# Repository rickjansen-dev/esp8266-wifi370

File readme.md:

esp8266-wifi370
==================

Implementation of the wifi370 protocol to connect cheap RGB ledstrips to pimatic using a esp8266.
Currently this repository contains the following:

 - Lua scripts to run on NodeMCU firmware
 - Eagle PCB schematic & board layout

## Quick how-to setup

- Install [pimatic] and the excellent [pimatic-led-light] plugin
- Install NodeMCU on the esp8266, connect it to your wifi & upload the lua scripts (ESPlorer is a nice tool to do this)

For the pimatic-led-light configuration, use wifi370 as the device parameter.
It's probably a good idea to set up your router's DHCP server so your esp8266 will get the same IP address every time.

## Eagle PCB schematic & board layout

There's a PCB schematic & board layout in the repository. The PCB contains the ESP-03, a voltage regulator, a power input & 3 logic gate MOSFETs to control the RGB channels of the ledstrip. See my blog at [auspex.nl] for a more detailed explanation.

## Demo video

I recorded a demonstration video, you can watch it [here].  
I am aware of VVS, it was just easier to get everything on screen and use my mouse at the same time =]

## Known bugs

- The PWM output sometimes glitches due to being software-based PWM. It only really flickers when moving from one color to another. 
- The output color is stored in the esp8266's flash memory. The pimatic-led-light UI can output a lot of values in a short amount of time which leads to lots of writes to the flash memory. I am unsure if this will be a problem and if the esp8266's flash can become corrupt. Use at your own risk.
- The on-off state might not always be in the correct state, as the wifi370 protocol implementation is very basic.

[pimatic]:http://pimatic.org
[pimatic-led-light]:https://github.com/philip1986/pimatic-led-light
[auspex.nl]:http://auspex.nl
[here]:http://youtu.be/MzmGHIzuEzY

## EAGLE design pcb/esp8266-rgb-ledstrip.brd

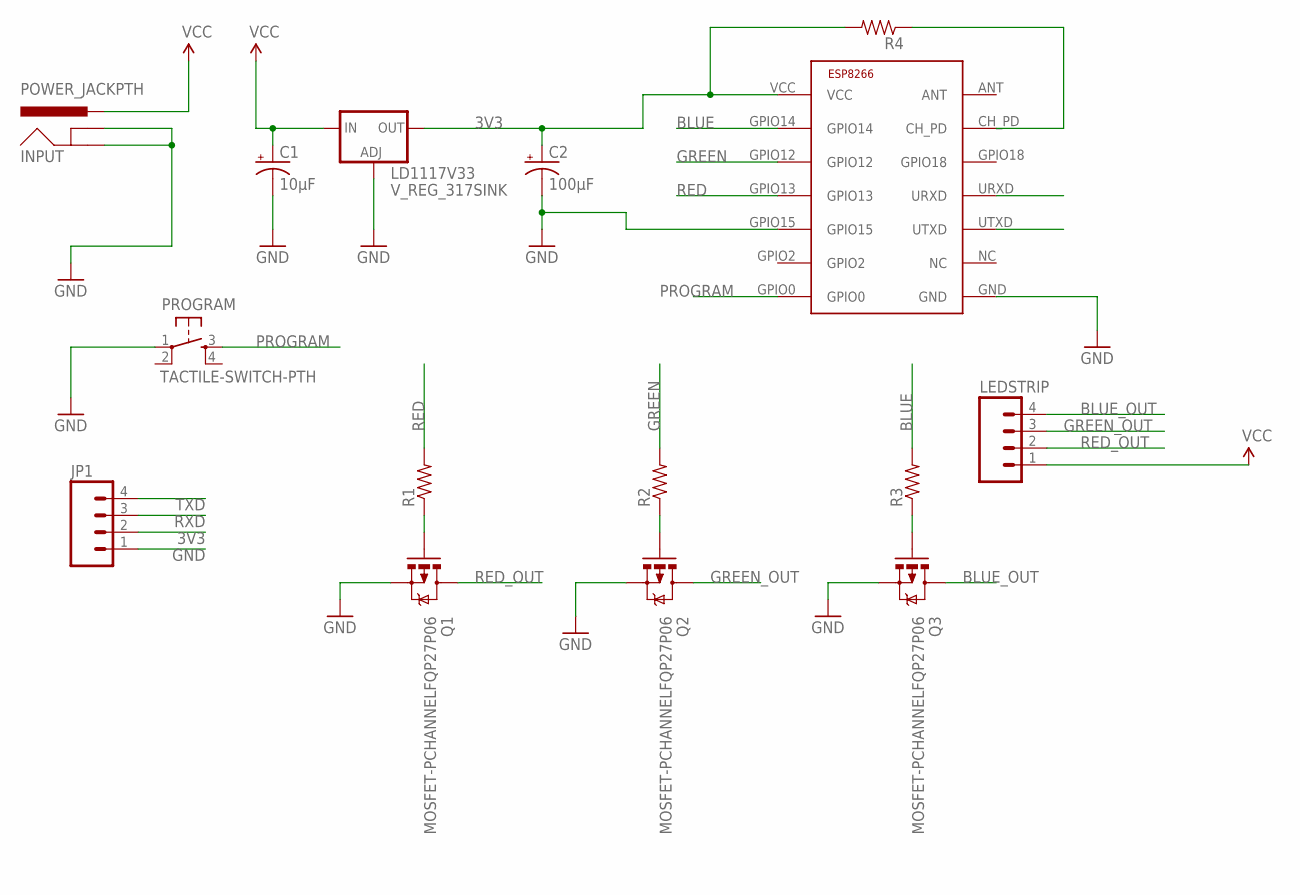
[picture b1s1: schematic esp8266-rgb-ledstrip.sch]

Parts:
C1: 10µF; CPOL-RADIAL-10UF-25V
C2: 100µF; CPOL-RADIAL-100UF-25V
INPUT: POWER_JACKPTH; POWER_JACK_PTH
JP1: M04PTH; 1X04
LD1117V33: V_REG_317SINK; TO220-ADJ
LEDSTRIP: M04PTH; 1X04
PROGRAM: TACTILE-SWITCH-PTH; TAC-SWITCH-PTH
Q1, Q2, Q3: MOSFET-PCHANNELFQP27P06; TO220V
R1, R2, R3, R4: RESISTORAXIAL-0.3; AXIAL-0.3
U$1: ESP8266-03; ESP-03

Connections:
3V3: C2.1 (+), JP1.2, LD1117V33.OUT, R4.P$2 (2), U$1.VCC
BLUE: R3.P$2 (2), U$1.GPIO14
BLUE_OUT: LEDSTRIP.4, Q3.2 (D)
BLUE_R: Q3.1 (G), R3.P$1 (1)
GND: C1.2 (-), C2.2 (-), INPUT.GND, INPUT.GNDBREAK, JP1.1, LD1117V33.ADJ, PROGRAM.1, Q1.3 (S), Q2.3 (S), Q3.3 (S), U$1.GND, U$1.GPIO15
GREEN: R2.P$2 (2), U$1.GPIO12
GREEN_OUT: LEDSTRIP.3, Q2.2 (D)
GREEN_R: Q2.1 (G), R2.P$1 (1)
unnamed: R4.P$1 (1), U$1.CH_PD
PROGRAM: PROGRAM.3, U$1.GPIO0
RED: R1.P$2 (2), U$1.GPIO13
RED_OUT: LEDSTRIP.2, Q1.2 (D)
RED_R: Q1.1 (G), R1.P$1 (1)
RXD: JP1.3, U$1.URXD
TXD: JP1.4, U$1.UTXD
VCC: C1.1 (+), INPUT.PWR, LD1117V33.IN, LEDSTRIP.1

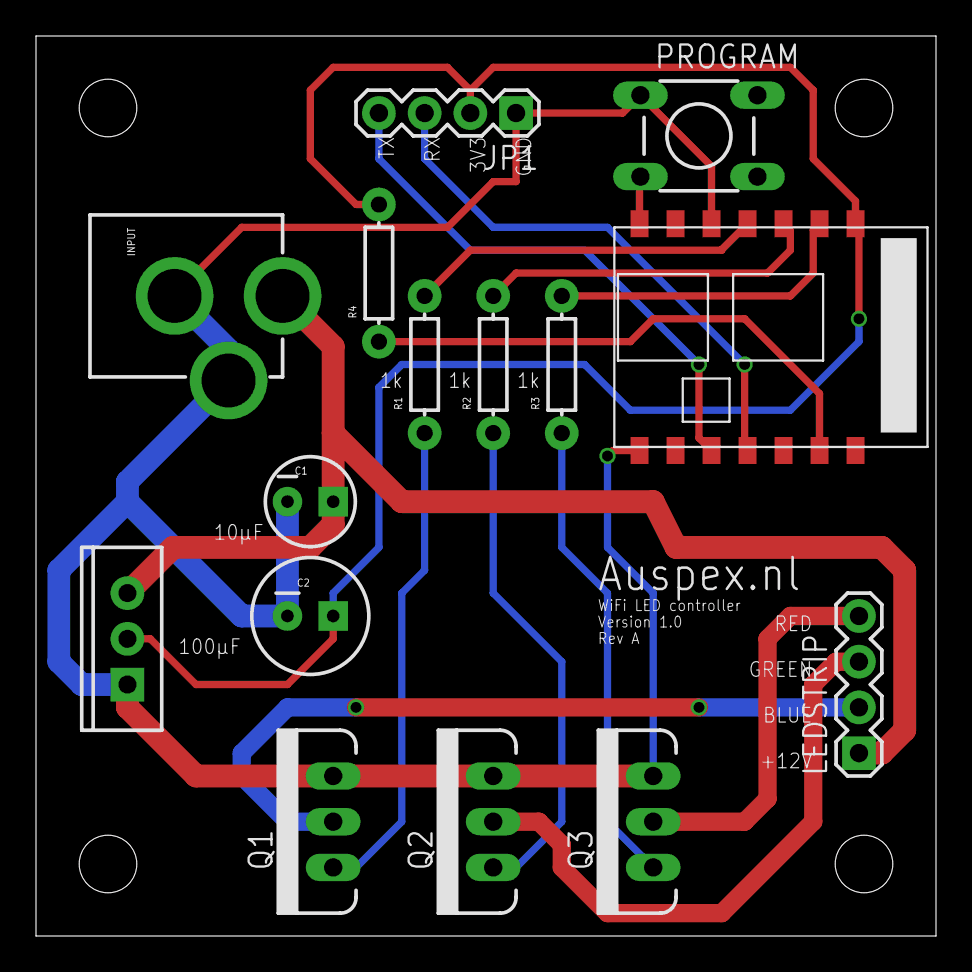
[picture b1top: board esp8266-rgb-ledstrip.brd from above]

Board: 2 copper layers, 50.0 x 50.0 mm, 15 parts (0 on the bottom side), 16 nets.

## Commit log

2015-05-07 initial commit of pcb files

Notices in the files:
parts and their libraries:
SparkFun-Capacitors: Licensing: Creative Commons ShareAlike 4.0 International - https://creativecommons.org/licenses/by-sa/4.0
